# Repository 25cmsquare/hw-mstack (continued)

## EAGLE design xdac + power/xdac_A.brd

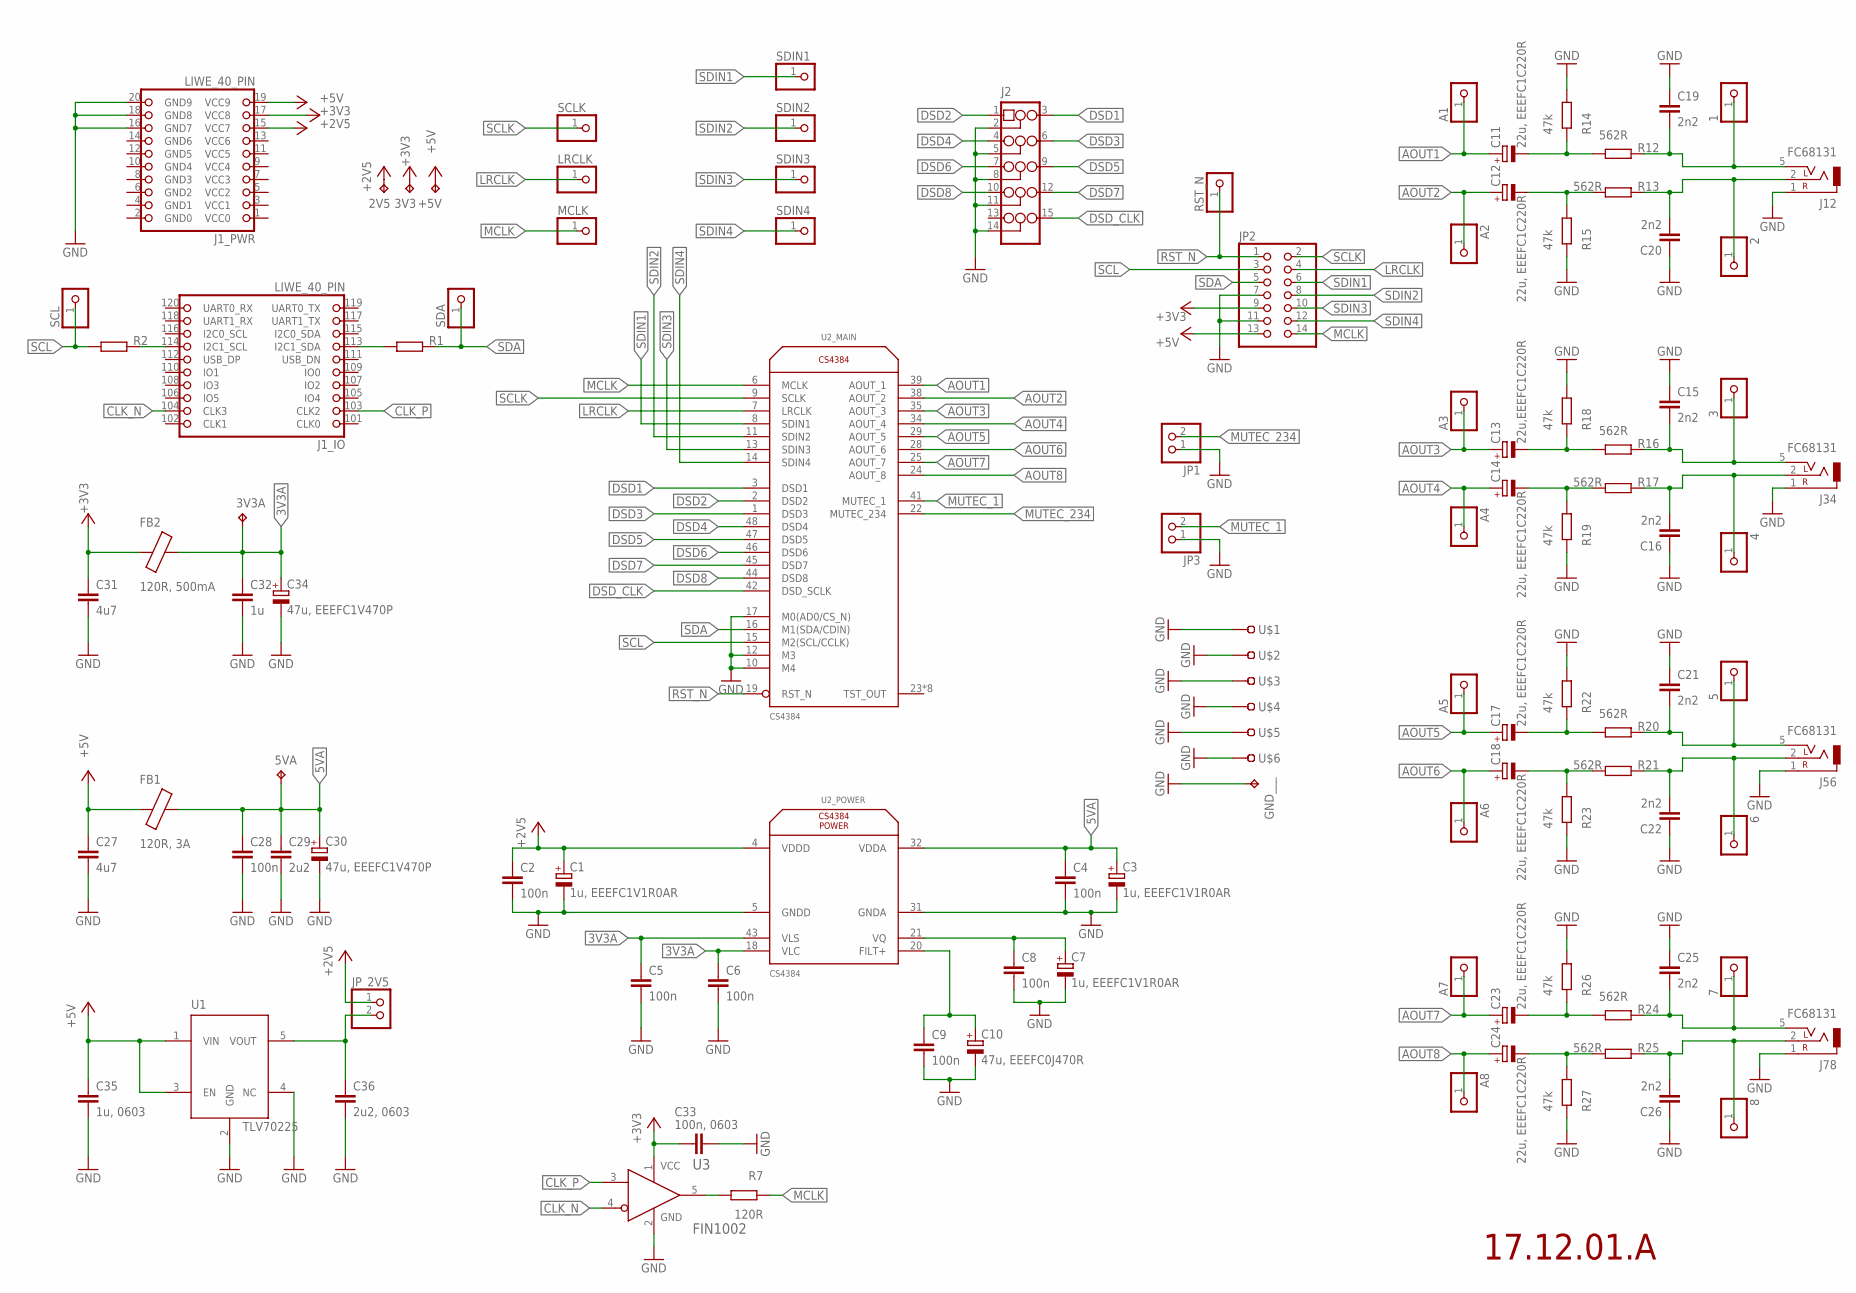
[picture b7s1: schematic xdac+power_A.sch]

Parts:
1, 2, 3, 4, 5, 6, 7, 8: PINHD-1X1; 1X01
2V5, 3V3, 3V3A, 5VA: TPTP14R; TP14R
+5V: TPTP14R; TP14R
A1, A2, A3, A4, A5, A6, A7, A8: PINHD-1X1; 1X01
C1, C3, C7: 1u, EEEFC1V1R0AR; EEE-FC1V1R0AR
C2, C4, C5, C8, C9: 100n; C0603
C6, C28: 100n; C0603K
C10: 47u, EEEFC0J470R; EEE-FC1C220R
C11, C12, C14, C17, C18, C23, C24: 22u, EEEFC1C220R; EEE-FC1C220R
C13: 22u,EEEFC1C220R; EEE-FC1C220R
C15, C16, C19, C20, C21, C22, C25, C26: 2n2; C0603
C27, C31: 4u7; C0603K
C29: 2u2; C0603K
C30, C34: 47u, EEEFC1V470P; EEE-FC1V470P
C32: 1u; C0603K
C33: 100n, 0603; C0603
C35: 1u, 0603; C0603
C36: 2u2, 0603; C0603
FB1: 120R, 3A; L0603
FB2: 120R, 500mA; L0603
GND___: TPTP14R; TP14R
J1: LIWE_40_PIN; LIWE_40_PIN_8X8
J2: PINHD-3X5/90; 3X05/90
J12, J34, J56, J78: FC68131
JP1, JP3: PINHD-1X2/90; 1X02/90
JP2: PINHD-2X7; 2X07
JP_2V5: PINHD-1X2; 1X02
LRCLK: PINHD-1X1; 1X01
MCLK: PINHD-1X1; 1X01
R1, R2: R-EU_R0603; R0603
R7: 120R; R0603
R12, R13, R16, R17, R20, R21, R24, R25: 562R; R0603
R14, R15, R18, R19, R22, R23, R26, R27: 47k; R0603
RST_N: PINHD-1X1; 1X01
SCL: PINHD-1X1; 1X01
SCLK: PINHD-1X1; 1X01
SDA: PINHD-1X1; 1X01
SDIN1, SDIN2, SDIN3, SDIN4: PINHD-1X1; 1X01
U1: TLV70225; SOT-23-5
U2: CS4384; LQFP_48
U3: FIN1002; SOT95P280X140-5N
U$1, U$2, U$3, U$4, U$5, U$6: TEST-22-MULTICOMP; TEST_1MM

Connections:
2V5_OUT: C36.1, JP_2V5.2, U1.5 (VOUT)
3V3A: 3V3A.TP, C5.1, C6.1, C32.1, C34.1 (+), FB2.1, U2.18 (VLC), U2.43 (VLS)
5VA: 5VA.TP, C3.1 (+), C4.1, C28.1, C29.1, C30.1 (+), FB1.1, U2.32 (VDDA)
+2V5: 2V5.TP, C1.1 (+), C2.1, J1.15 (VCC7), JP_2V5.1, U2.4 (VDDD)
+3V3: 3V3.TP, C31.1, C33.2, FB2.2, J1.17 (VCC8), JP2.9, U3.1 (VCC)
+5V: +5V.TP, C27.1, C35.1, FB1.2, J1.19 (VCC9), JP2.13, U1.1 (VIN), U1.3 (EN)
AOUT1: A1.1, C11.1 (+), U2.39 (AOUT_1)
AOUT2: A2.1, C12.1 (+), U2.38 (AOUT_2)
AOUT2_: 2.1, C20.2, J12.2, R13.2
AOUT3: A3.1, C13.1 (+), U2.35 (AOUT_3)
AOUT3_: 3.1, C15.2, J34.5 (3), R16.2
AOUT4: A4.1, C14.1 (+), U2.34 (AOUT_4)
AOUT4_: 4.1, C16.2, J34.2, R17.2
AOUT5: A5.1, C17.1 (+), U2.29 (AOUT_5)
AOUT5_: 5.1, C21.2, J56.5 (3), R20.2
AOUT6: A6.1, C18.1 (+), U2.28 (AOUT_6)
AOUT6_: 6.1, C22.2, J56.2, R21.2
AOUT7: A7.1, C23.1 (+), U2.25 (AOUT_7)
AOUT7_: 7.1, C25.2, J78.5 (3), R24.2
AOUT8: A8.1, C24.1 (+), U2.24 (AOUT_8)
AOUT8_: 8.1, C26.2, J78.2, R25.2
AUOT1_: 1.1, C19.2, J12.5 (3), R12.2
CLK_N: J1.104 (CLK3), U3.4 (RIN-)
CLK_P: J1.103 (CLK2), U3.3 (RIN+)
DSD1: J2.3, U2.3 (DSD1)
DSD2: J2.1, U2.2 (DSD2)
DSD3: J2.6, U2.1 (DSD3)
DSD4: J2.4, U2.48 (DSD4)
DSD5: J2.9, U2.47 (DSD5)
DSD6: J2.7, U2.46 (DSD6)
DSD7: J2.12, U2.45 (DSD7)
DSD8: J2.10, U2.44 (DSD8)
DSD_CLK: J2.15, U2.42 (DSD_SCLK)
FILT+: C9.1, C10.1 (+), U2.20 (FILT+)
GND: C1.2 (-), C2.2, C3.2 (-), C4.2, C5.2, C6.2, C7.2 (-), C8.2, C9.2, C10.2 (-), C15.1, C16.1, C19.1, C20.1, C21.1, C22.1, C25.1, C26.1, C27.2, C28.2, C29.2, C30.2 (-), C31.2, C32.2, C33.1, C34.2 (-), C35.2, C36.2, GND___.TP, J1.16 (GND7), J1.18 (GND8), J1.20 (GND9), J2.2, J2.5, J2.8, J2.11, J2.14, J12.1, J34.1, J56.1, J78.1, JP1.1, JP2.7, JP2.11, JP3.1, R14.2, R15.1, R18.2, R19.1, R22.2, R23.1, R26.2, R27.1, U1.2 (GND), U1.4 (NC), U2.5 (GNDD), U2.10 (M4), U2.12 (M3), U2.17 (M0(AD0/CS_N)), U2.31 (GNDA), U3.2 (GND), U$1.1, U$2.1, U$3.1, U$4.1, U$5.1, U$6.1
LRCLK: JP2.4, LRCLK.1, U2.7 (LRCLK)
MCLK: JP2.14, MCLK.1, R7.1, U2.6 (MCLK)
MUTEC_1: JP3.2, U2.41 (MUTEC_1)
MUTEC_234: JP1.2, U2.22 (MUTEC_234)
unnamed: J1.113 (I2C1_SDA), R1.1
unnamed: J1.114 (I2C1_SCL), R2.2
unnamed: R7.2, U3.5 (ROUT)
unnamed: C11.2 (-), R12.1, R14.1
unnamed: C12.2 (-), R13.1, R15.2
unnamed: C13.2 (-), R16.1, R18.1
unnamed: C14.2 (-), R17.1, R19.2
unnamed: C17.2 (-), R20.1, R22.1
unnamed: C18.2 (-), R21.1, R23.2
unnamed: C23.2 (-), R24.1, R26.1
unnamed: C24.2 (-), R25.1, R27.2
RST_N: JP2.1, RST_N.1, U2.19 (RST_N)
SCL: JP2.3, R2.1, SCL.1, U2.15 (M2(SCL/CCLK))
SCLK: JP2.2, SCLK.1, U2.9 (SCLK)
SDA: JP2.5, R1.2, SDA.1, U2.16 (M1(SDA/CDIN))
SDIN1: JP2.6, SDIN1.1, U2.8 (SDIN1)
SDIN2: JP2.8, SDIN2.1, U2.11 (SDIN2)
SDIN3: JP2.10, SDIN3.1, U2.13 (SDIN3)
SDIN4: JP2.12, SDIN4.1, U2.14 (SDIN4)
VQ: C7.1 (+), C8.1, U2.21 (VQ)

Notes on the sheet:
17.12.01.A

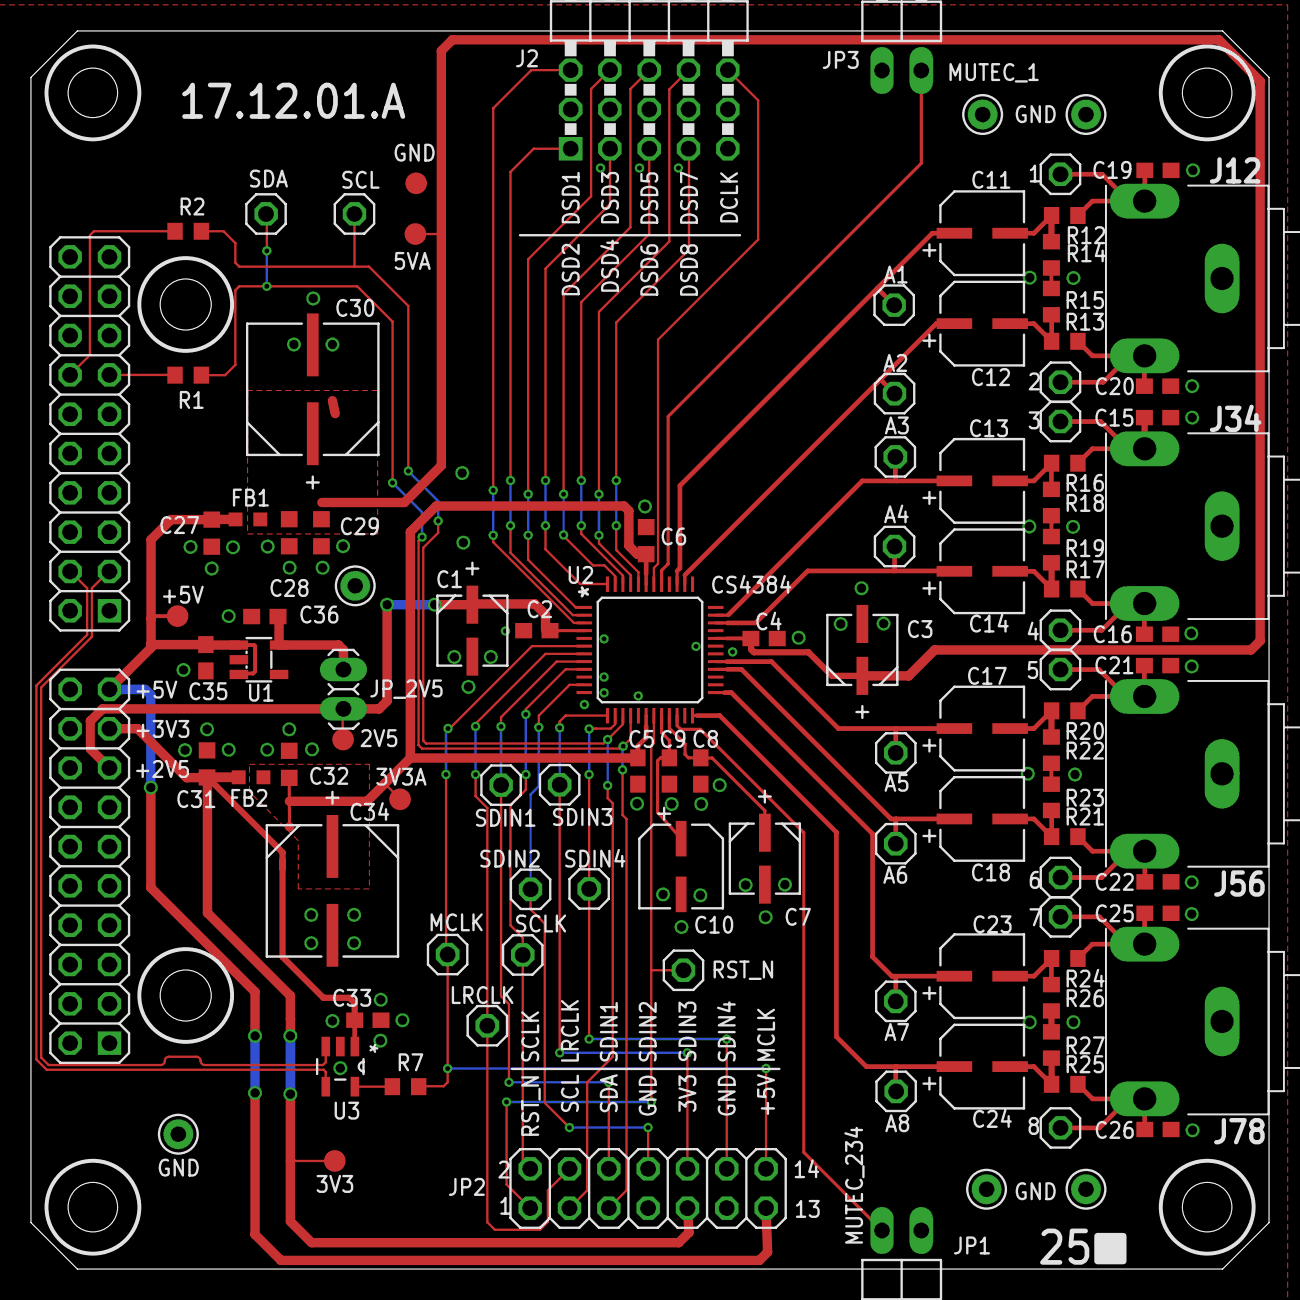
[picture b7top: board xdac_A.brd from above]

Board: 2 copper layers, 80.0 x 80.0 mm, 108 parts (0 on the bottom side), 59 nets.

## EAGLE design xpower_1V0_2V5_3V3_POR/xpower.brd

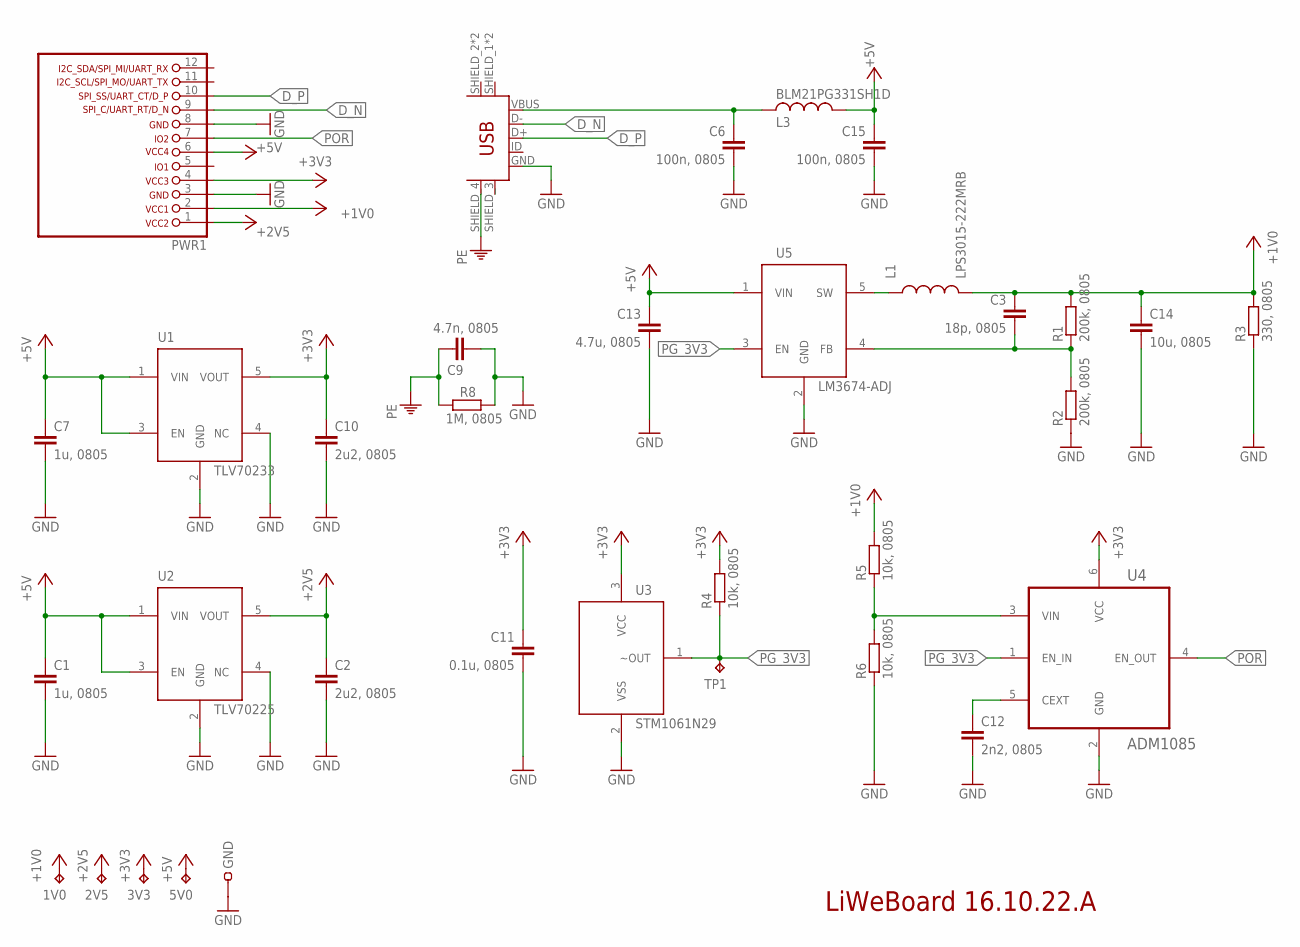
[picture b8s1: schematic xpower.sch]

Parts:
1V0, 2V5, 3V3, 5V0: TPTP14R; TP14R
C1, C7: 1u, 0805; C0805
C2, C10: 2u2, 0805; C0805
C3: 18p, 0805; C0805
C6, C15: 100n, 0805; C0805
C9: 4.7n, 0805; C0805
C11: 0.1u, 0805; C0805
C12: 2n2, 0805; C0805
C13: 4.7u, 0805; C0805
C14: 10u, 0805; C0805
GND: TEST-22-MULTICOMP; TEST_1MM
L1: LPS3015-222MRB; LPS3015
L3: BLM21PG331SH1D; R0805
PWR1: LIWE_12_PIN_PWR; LIWE_12_PIN
R1, R2: 200k, 0805; R0805
R3: 330, 0805; R0805
R4, R5, R6: 10k, 0805; R0805
R8: 1M, 0805; R0805
TP1: TPTP14R; TP14R
U1: TLV70233; SOT-23-5
U2: TLV70225; SOT-23-5
U3: STM1061N29; SOT-23-3
U4: ADM1085; SOT65P210X110-6N
U5: LM3674-ADJ; SOT-23-5
U$5: ZX62D-B-5PA8

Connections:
+1V0: 1V0.TP, C3.1, C14.1, L1.P2 (2), PWR1.2, R1.2, R3.2, R5.2
+2V5: 2V5.TP, C2.1, PWR1.1, U2.5 (VOUT)
+3V3: 3V3.TP, C10.1, C11.1, PWR1.4, R4.2, U1.5 (VOUT), U3.3 (VCC), U4.6 (VCC)
+5V: 5V0.TP, C1.1, C7.1, C13.1, C15.1, L3.1, PWR1.6, U1.1 (VIN), U1.3 (EN), U2.1 (VIN), U2.3 (EN), U5.1 (VIN)
CEXT: C12.1, U4.5 (CEXT)
D_N: PWR1.9, U$5.D-
D_P: PWR1.10, U$5.D+
FB: C3.2, R1.1, R2.2, U5.4 (FB)
GND: C1.2, C2.2, C6.2, C7.2, C9.2, C10.2, C11.2, C12.2, C13.2, C14.2, C15.2, GND.1, PWR1.3, PWR1.8, R2.1, R3.1, R6.1, R8.1, U1.2 (GND), U1.4 (NC), U2.2 (GND), U2.4 (NC), U3.2 (VSS), U4.2 (GND), U5.2 (GND), U$5.GND
L: L1.P1 (1), U5.5 (SW)
PE: C9.1, R8.2, U$5.SHIELD_4 (MTN4)
PG_3V3: R4.1, TP1.TP, U3.1 (~OUT), U4.1 (EN_IN), U5.3 (EN)
POR: PWR1.7, U4.4 (EN_OUT)
VBUS: C6.1, L3.2, U$5.VBUS
VIN: R5.1, R6.2, U4.3 (VIN)

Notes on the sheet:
LiWeBoard 16.10.22.A

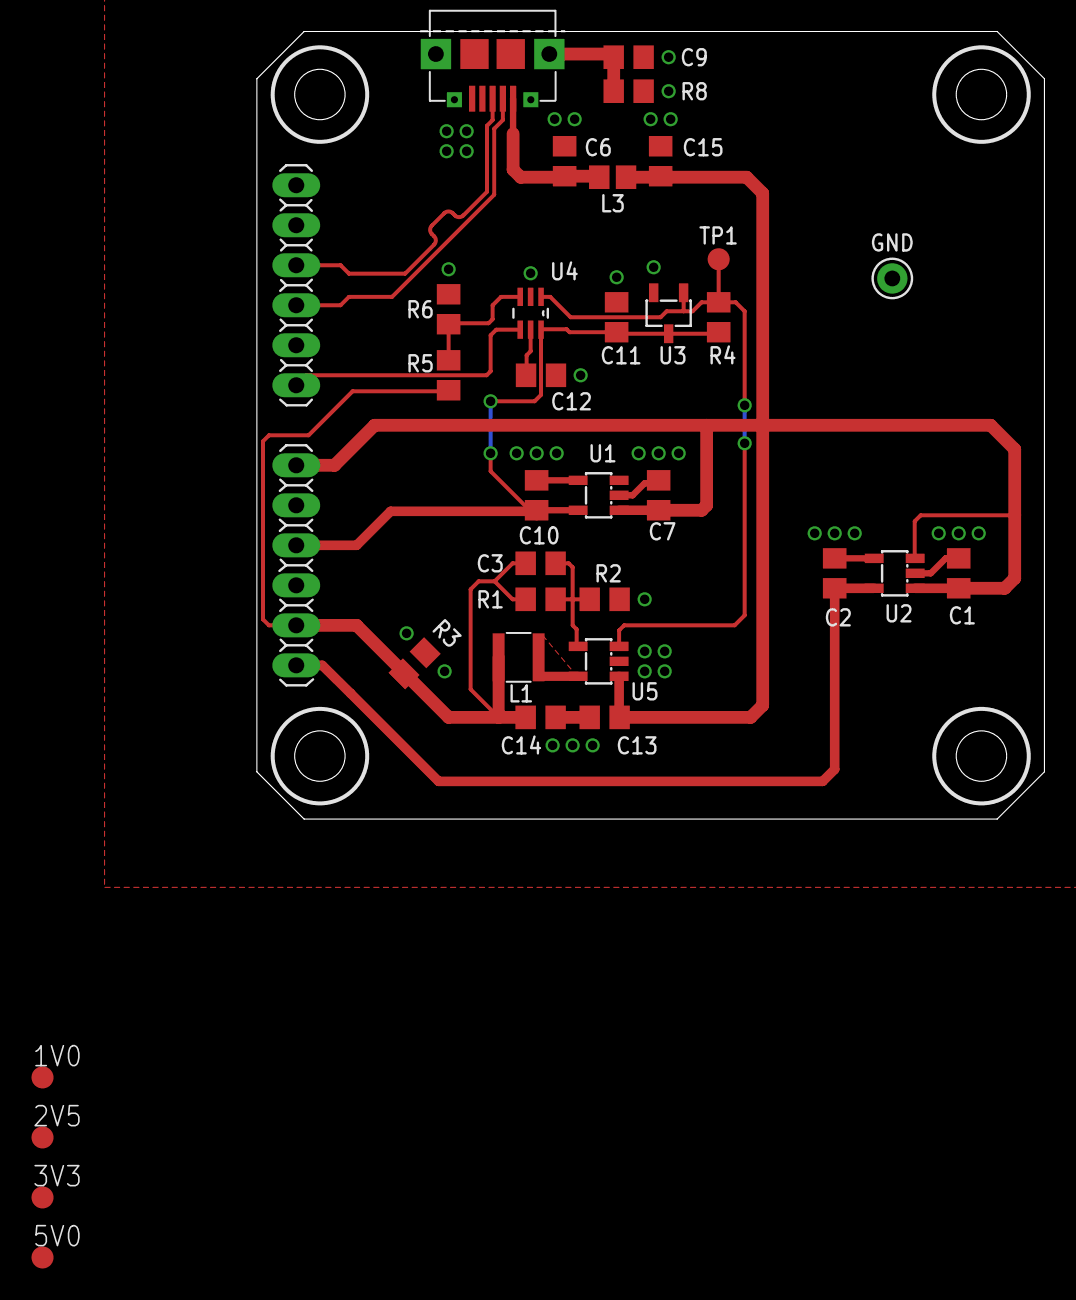
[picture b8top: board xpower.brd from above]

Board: 2 copper layers, 50.0 x 50.0 mm, 34 parts (1 on the bottom side), 15 nets.
